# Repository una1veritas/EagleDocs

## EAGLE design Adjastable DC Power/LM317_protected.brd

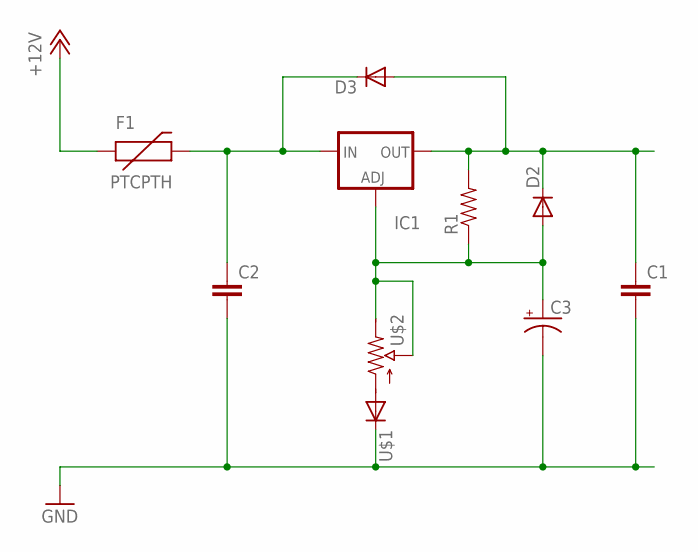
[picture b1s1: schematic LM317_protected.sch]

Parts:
C1, C2: CAPKIT; CAP-PTH-SMALL-KIT
C3: CAP_POLPTH2; CPOL-RADIAL-10UF-25V
D2, D3: DIODEPTH; DIODE-1N4001
F1: PTCPTH; PTC
IC1: LM337TS; 337TS
R1: RESISTORAXIAL-0.3; AXIAL-0.3
U$1: DIODE1N4148; DIODE-1N4148
U$2: POT100K_3362U; 3362U

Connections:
+12V: F1.P$1 (1)
AGND: C1.2, C2.2, C3.2 (-), U$1.C
unnamed: C3.1 (+), D2.A, IC1.1 (ADJ), R1.P$1 (1), U$2.P$1 (E), U$2.P$2 (S)
unnamed: C1.1, D2.C, D3.A, IC1.3 (OUT), R1.P$2 (2)
unnamed: C2.1, D3.C, F1.P$2 (2), IC1.2 (IN)
unnamed: U$1.A, U$2.P$3 (A)

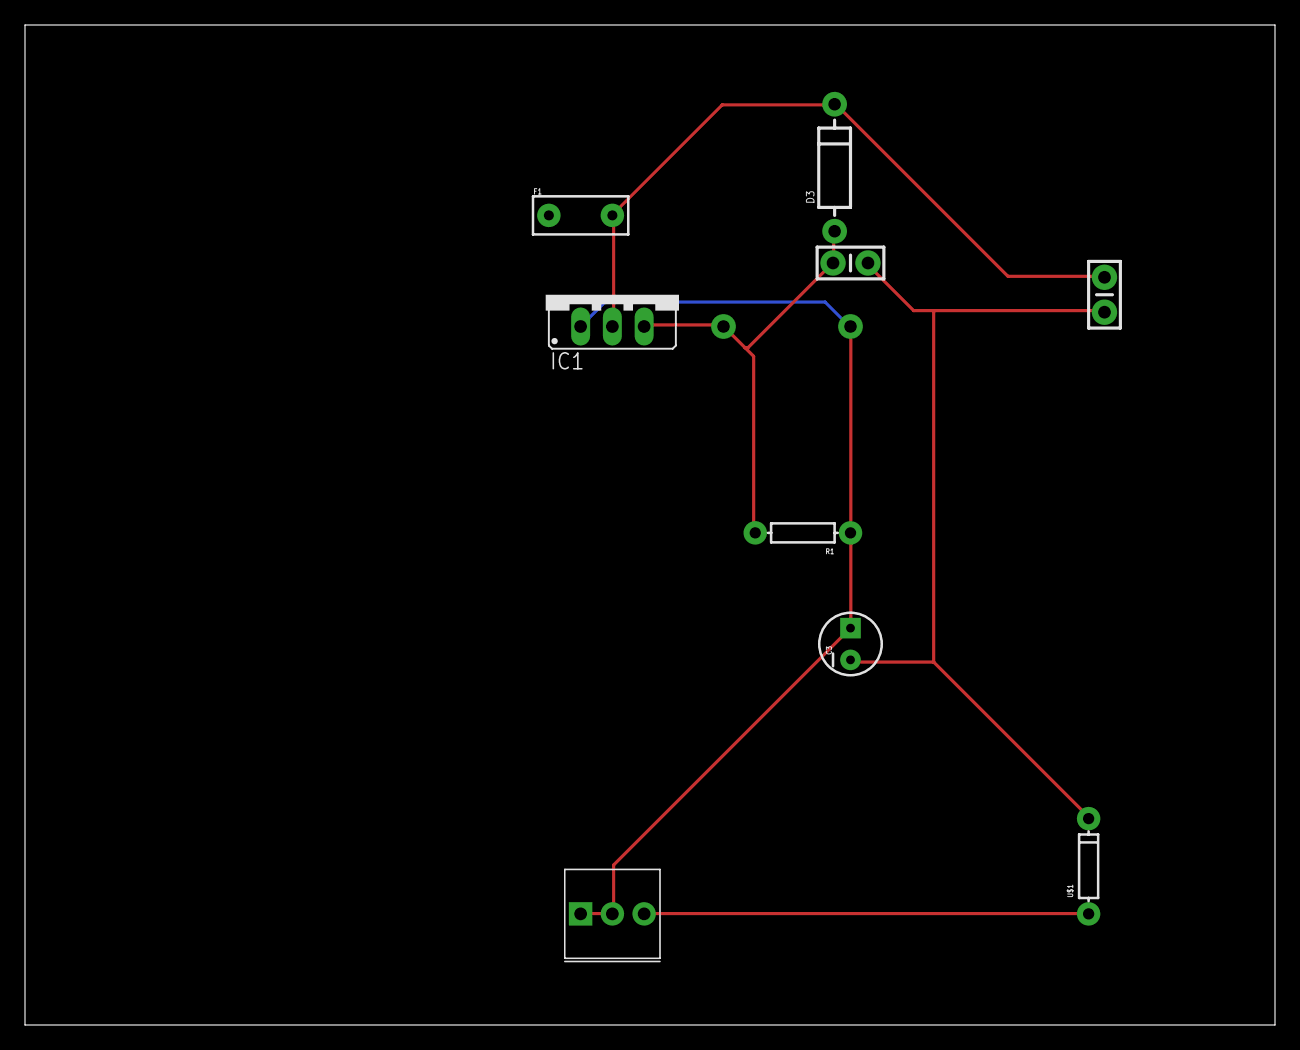
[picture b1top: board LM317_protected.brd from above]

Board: 2 copper layers, 100.0 x 80.0 mm, 10 parts (1 on the bottom side), 5 nets.

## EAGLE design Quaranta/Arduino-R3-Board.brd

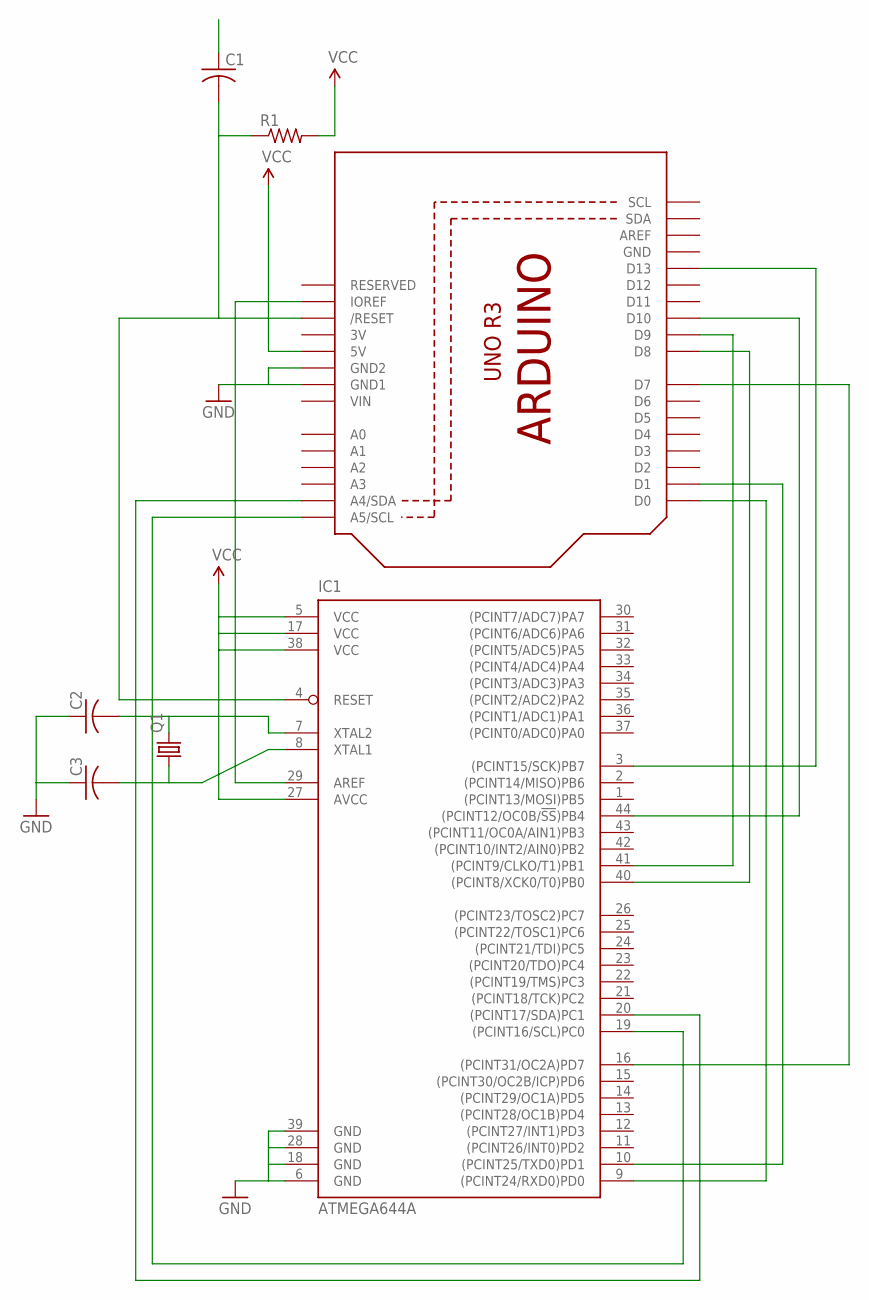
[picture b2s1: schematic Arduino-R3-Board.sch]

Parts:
C1, C2, C3: C-US025-024X044; C025-024X044
IC1: ATMEGA644A; TQFP44
Q1: CRYSTALHC49S; HC49/S
R1: R-US_0204/7; 0204/7
U1: ARDUINOR3-BPLACE

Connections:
3V: U1.3V
GND: C2.1, C3.1, IC1.6 (GND), IC1.18 (GND), IC1.28 (GND), IC1.39 (GND), U1.GND, U1.GND1, U1.GND2
unnamed: C1.2, IC1.4 (RESET), R1.1, U1.RESET (/RESET)
unnamed: IC1.29 (AREF), U1.IOREF
unnamed: IC1.9 ((PCINT24/RXD0)PD0), U1.D0
unnamed: IC1.10 ((PCINT25/TXD0)PD1), U1.D1
unnamed: IC1.16 ((PCINT31/OC2A)PD7), U1.D7
unnamed: IC1.3 ((PCINT15/SCK)PB7), U1.D13
unnamed: IC1.44 ((PCINT12/OC0B/!SS!)PB4), U1.D10
unnamed: IC1.40 ((PCINT8/XCK0/T0)PB0), U1.D8
unnamed: IC1.41 ((PCINT9/CLKO/T1)PB1), U1.D9
unnamed: IC1.19 ((PCINT16/SCL)PC0), U1.A5 (A5/SCL)
unnamed: IC1.20 ((PCINT17/SDA)PC1), U1.A4 (A4/SDA)
unnamed: C2.2, IC1.7 (XTAL2), Q1.2
unnamed: C3.2, IC1.8 (XTAL1), Q1.1
VCC: IC1.5 (VCC), IC1.17 (VCC), IC1.27 (AVCC), IC1.38 (VCC), R1.2, U1.5V
VIN: U1.VIN

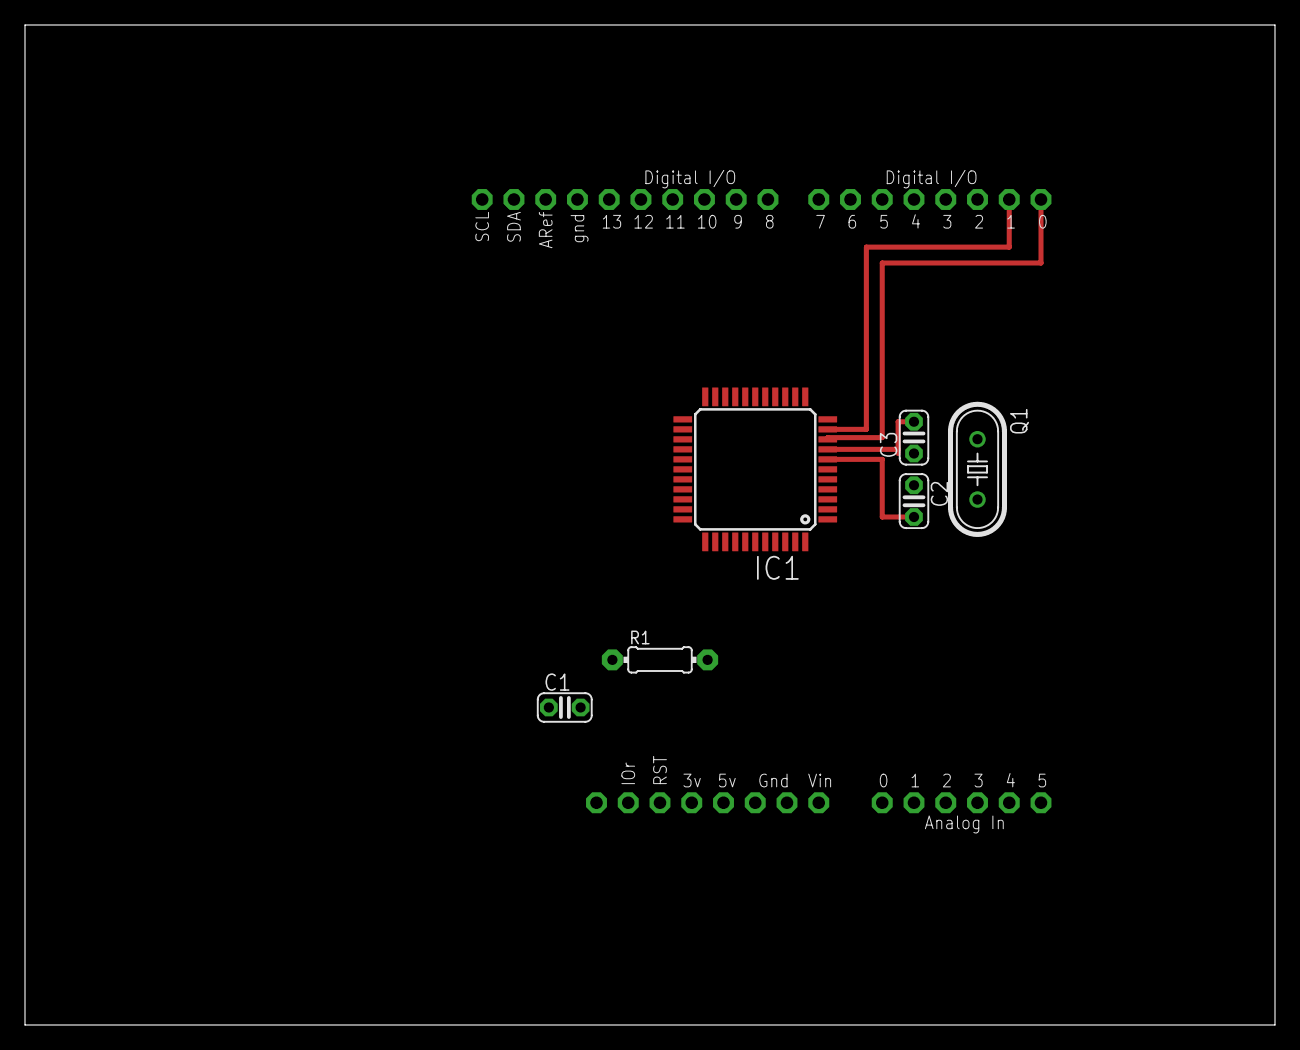
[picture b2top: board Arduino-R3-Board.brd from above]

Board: 2 copper layers, 100.0 x 80.0 mm, 7 parts (0 on the bottom side), 15 nets.

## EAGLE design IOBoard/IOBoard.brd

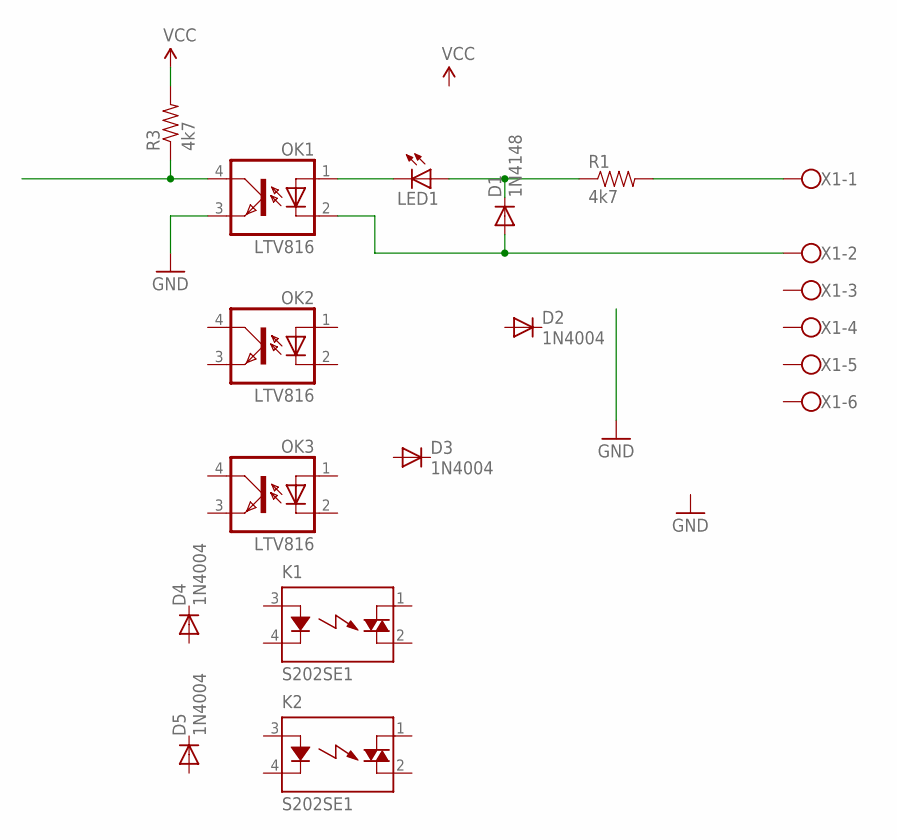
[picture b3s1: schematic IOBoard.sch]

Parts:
D1: 1N4148; DO34-5
D2, D3, D4, D5: 1N4004; DO41-10
K1, K2: S202SE1; S2XXEX
LED1: LED3MM
OK1, OK2, OK3: LTV816; DIL04
R1, R3: 4k7; 1/6W-RES
X1: W237-6

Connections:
GND: OK1.3 (EMIT)
unnamed: LED1.K (C), OK1.1 (A)
unnamed: R1.2, X1.1
unnamed: D1.A, OK1.2 (C), X1.2
unnamed: D1.C, LED1.A, R1.1
unnamed: OK1.4 (COL), R3.1
VCC: R3.2

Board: 2 copper layers, 14 parts (0 on the bottom side), 5 nets, no tracks yet.

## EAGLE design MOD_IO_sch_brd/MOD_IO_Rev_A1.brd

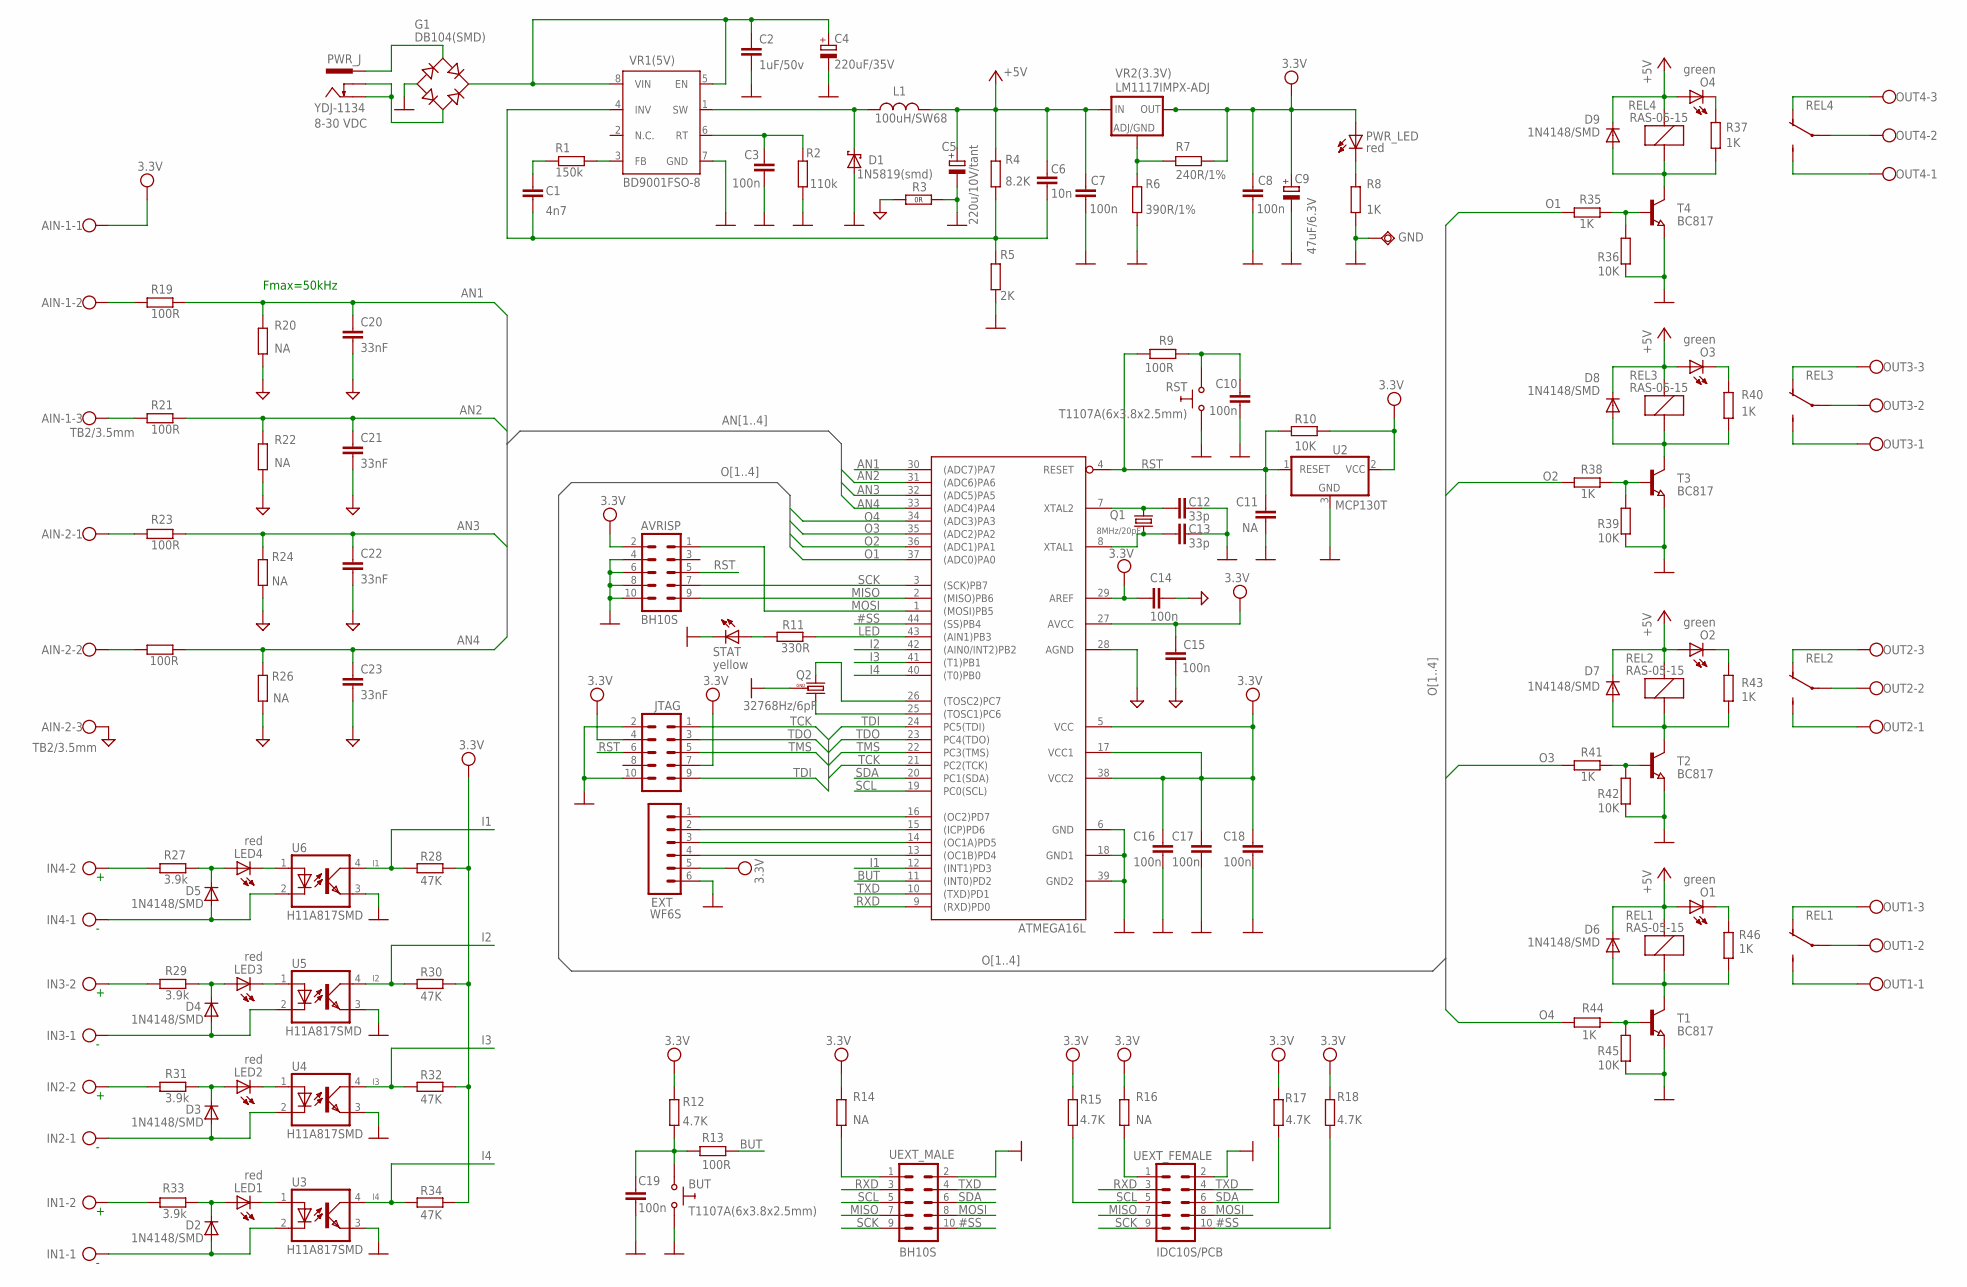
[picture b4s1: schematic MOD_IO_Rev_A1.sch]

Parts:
AIN-1, AIN-2: TB2/3.5mm; CON3-3.5MM
AVRISP: BH10S; CON2X5_SS2
BUT: T1107A(6x3.8x2.5mm); SW-TAKT_6X3.5_SMD
C1: 4n7; C0603
C2: 1uF/50v; C0805
C3, C7, C8, C10, C14, C15, C16, C17, C18, C19: 100n; C0603
C4: 220uF/35V; E3,5-8
C5: 220u/10V/tant; CT7343
C6: 10n; C0603
C9: 47uF/6.3V; CT3528
C11: NA; C0603
C12, C13: 33p; C0603
C20, C21, C22, C23: 33nF; C0603
D1: 1N5819(smd); MLL-41
D2, D3, D4, D5, D6, D7, D8, D9: 1N4148/SMD; SOD80C
EXT: WF6S; CON2.54MM-6-0
G1: DB104(SMD); DB104_SMD
GND: TESTPAD40/70; TESTPAD
IN1, IN2, IN3, IN4: TB2/5MM; W237-102
JTAG: BH10S; CON2X5_SS2
L1: 100uH/SW68; SW68
LED1, LED2, LED3, LED4: red; LED-0805
O1, O2, O3, O4: green; LED-0805
OUT1, OUT2, OUT3, OUT4: TB3/5MM; W237-103
PWR_J: YDJ-1134; PWR_JACK_UNI
PWR_LED: red; LED-0805
Q1: 8MHz/20pF; HC49/SMD2_THIN
Q2: 32768Hz/6pF; TC26H_3_REPAIR
R1: 150k; R0603
R2: 110k; R0603
R3: R_0R0R(NA); 0603_0R
R4: 8.2K; R0603
R5: 2K; R0603
R6: 390R/1%; R0603
R7: 240R/1%; R0603
R8, R35, R37, R38, R40, R41, R43, R44, R46: 1K; R0603
R9, R13, R19, R21, R23, R25: 100R; R0603
R10, R36, R39, R42, R45: 10K; R0603
R11: 330R; R0603
R12, R15, R17, R18: 4.7K; R0603
R14, R16, R20, R22, R24, R26: NA; R0603_NA
R27, R29, R31, R33: 3.9k; R0603
R28, R30, R32, R34: 47K; R0603
REL1, REL2, REL3, REL4: RAS-05-15; H200-FAT
RST: T1107A(6x3.8x2.5mm); SW-TAKT_6X3.5_SMD
STAT: yellow; LED-0805
T1, T2, T3, T4: BC817; SOT23
U1: ATMEGA16L; 44TQFP
U2: MCP130T; SOT23
U3, U4, U5, U6: H11A817SMD; OPTOCOUPLER_SMD4PIN
UEXT_FEMALE: IDC10S/PCB; ML10L_PADS_FEMAIL
UEXT_MALE: BH10S; ML10_PADS
VR1(5V): BD9001FSO-8; SO-8
VR2(3.3V): LM1117IMPX-ADJ; SOT223

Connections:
#SS: R18.1, U1.44 ((SS)PB4), UEXT_FEMALE.10, UEXT_MALE.10
+5V: C5.+, C6.1, C7.2, D6.C, D7.C, D8.C, D9.C, L1.2, O1.A, O2.A, O3.A, O4.A, R4.1, REL1.1, REL2.1, REL3.1, REL4.1, VR2(3.3V).3 (IN)
AGND: AIN-2.3, C14.2, C15.1, C20.2, C21.2, C22.2, C23.2, R3.1 (1.1), R20.1, R22.1, R24.1, R26.1, U1.28 (AGND)
AN1: C20.1, R19.2, R20.2, U1.30 ((ADC7)PA7)
AN2: C21.1, R21.2, R22.2, U1.31 ((ADC6)PA6)
AN3: C22.1, R23.2, R24.2, U1.32 ((ADC5)PA5)
AN4: C23.1, R25.1, R26.2, U1.33 ((ADC4)PA4)
BUT: R13.2, U1.11 ((INT0)PD2)
GND: AVRISP.4, AVRISP.6, AVRISP.8, AVRISP.10, BUT.P$1 (0), C2.2, C3.1, C4.-, C5.-, C7.1, C8.1, C9.-, C10.2, C11.2, C12.1, C13.1, C16.2, C17.2, C18.2, C19.2, D1.A, EXT.6, G1.-, GND.P$1, JTAG.2, JTAG.10, Q2.GND, R2.2, R3.2 (1.2), R5.2, R6.2, R8.2, R36.1, R39.1, R42.1, R45.1, RST.P$1 (0), STAT.C, T1.2 (E), T2.2 (E), T3.2 (E), T4.2 (E), U1.6 (GND), U1.18 (GND1), U1.39 (GND2), U2.3 (GND), U3.3 (EMI), U4.3 (EMI), U5.3 (EMI), U6.3 (EMI), UEXT_FEMALE.2, UEXT_MALE.2, VR1(5V).7 (GND)
I1: R28.1, U1.12 ((INT1)PD3), U6.4 (COL)
I2: R30.1, U1.42 ((AIN0/INT2)PB2), U5.4 (COL)
I3: R32.1, U1.41 ((T1)PB1), U4.4 (COL)
I4: R34.1, U1.40 ((T0)PB0), U3.4 (COL)
LED: R11.1, U1.43 ((AIN1)PB3)
MISO: AVRISP.9, U1.2 ((MISO)PB6), UEXT_FEMALE.7, UEXT_MALE.7
MOSI: AVRISP.1, U1.1 ((MOSI)PB5), UEXT_FEMALE.8, UEXT_MALE.8
unnamed: BUT.P$2 (1), C19.1, R12.2, R13.1
unnamed: R16.1, UEXT_FEMALE.1
unnamed: OUT2.2, REL2.P
unnamed: OUT2.1, REL2.S
unnamed: OUT4.3, REL4.O
unnamed: OUT1.2, REL1.P
unnamed: OUT1.1, REL1.S
unnamed: IN4.2, R27.1
unnamed: IN3.2, R29.1
unnamed: IN2.2, R31.1
unnamed: IN1.2, R33.1
unnamed: R14.1, UEXT_MALE.1
unnamed: EXT.1, U1.16 ((OC2)PD7)
unnamed: C10.1, R9.1, RST.P$2 (1)
unnamed: OUT4.2, REL4.P
unnamed: OUT4.1, REL4.S
unnamed: R35.2, R36.2, T4.1 (B)
unnamed: OUT3.3, REL3.O
unnamed: D9.A, R37.1, REL4.2, T4.3 (C)
unnamed: OUT3.2, REL3.P
unnamed: OUT3.1, REL3.S
unnamed: R38.2, R39.2, T3.1 (B)
unnamed: O4.C, R37.2
unnamed: O3.C, R40.2
unnamed: C12.2, Q1.2, U1.7 (XTAL2)
unnamed: OUT2.3, REL2.O
unnamed: EXT.2, U1.15 ((ICP)PD6)
unnamed: EXT.3, U1.14 ((OC1A)PD5)
unnamed: R41.2, R42.2, T2.1 (B)
unnamed: O1.C, R46.2
unnamed: D8.A, R40.1, REL3.2, T3.3 (C)
unnamed: EXT.4, U1.13 ((OC1B)PD4)
unnamed: OUT1.3, REL1.O
unnamed: R44.2, R45.2, T1.1 (B)
unnamed: C1.1, C6.2, R4.2, R5.1, VR1(5V).4 (INV)
unnamed: O2.C, R43.2
unnamed: D7.A, R43.1, REL2.2, T2.3 (C)
unnamed: D6.A, R46.1, REL1.2, T1.3 (C)
unnamed: R1.1, VR1(5V).3 (FB)
unnamed: R11.2, STAT.A
unnamed: G1.AC1, PWR_J.-, PWR_J.--
unnamed: G1.AC2, PWR_J.+
unnamed: AIN-1.2, R19.1
unnamed: C13.2, Q1.1, U1.8 (XTAL1)
unnamed: AIN-2.2, R25.2
unnamed: C1.2, R1.2
unnamed: R6.1, R7.1, VR2(3.3V).1 (ADJ/GND)
unnamed: AIN-1.3, R21.1
unnamed: PWR_LED.C, R8.1
unnamed: AIN-2.1, R23.1
unnamed: C2.1, C4.+, G1.+, VR1(5V).5 (EN), VR1(5V).8 (VIN)
unnamed: C3.2, R2.1, VR1(5V).6 (RT)
unnamed: D4.A, IN3.1, U5.2 (C)
unnamed: LED3.C, U5.1 (A)
unnamed: D5.C, LED4.A, R27.2
unnamed: D5.A, IN4.1, U6.2 (C)
unnamed: D1.K (C), L1.1, VR1(5V).1 (SW)
unnamed: LED4.C, U6.1 (A)
unnamed: D4.C, LED3.A, R29.2
unnamed: D2.A, IN1.1, U3.2 (C)
unnamed: Q2.1, U1.26 ((TOSC2)PC7)
unnamed: LED1.C, U3.1 (A)
unnamed: D3.C, LED2.A, R31.2
unnamed: D3.A, IN2.1, U4.2 (C)
unnamed: Q2.2, U1.25 ((TOSC1)PC6)
unnamed: LED2.C, U4.1 (A)
unnamed: D2.C, LED1.A, R33.2
O1: R35.1, U1.37 ((ADC0)PA0)
O2: R38.1, U1.36 ((ADC1)PA1)
O3: R41.1, U1.35 ((ADC2)PA2)
O4: R44.1, U1.34 ((ADC3)PA3)
RST: AVRISP.5, C11.1, JTAG.6, R9.2, R10.2, U1.4 (RESET), U2.1 (RESET)
RXD: U1.9 ((RXD)PD0), UEXT_FEMALE.3, UEXT_MALE.3
SCK: AVRISP.7, U1.3 ((SCK)PB7), UEXT_FEMALE.9, UEXT_MALE.9
SCL: R15.1, U1.19 (PC0(SCL)), UEXT_FEMALE.5, UEXT_MALE.5
SDA: R17.1, U1.20 (PC1(SDA)), UEXT_FEMALE.6, UEXT_MALE.6
TCK: JTAG.1, U1.21 (PC2(TCK))
TDI: JTAG.9, U1.24 (PC5(TDI))
TDO: JTAG.3, U1.23 (PC4(TDO))
TMS: JTAG.5, U1.22 (PC3(TMS))
TXD: U1.10 ((TXD)PD1), UEXT_FEMALE.4, UEXT_MALE.4
VCC: AIN-1.1, AVRISP.2, C8.2, C9.+, C14.1, C15.2, C16.1, C17.1, C18.1, EXT.5, JTAG.4, JTAG.7, PWR_LED.A, R7.2, R10.1, R12.1, R14.2, R15.2, R16.2, R17.2, R18.2, R28.2, R30.2, R32.2, R34.2, U1.5 (VCC), U1.17 (VCC1), U1.27 (AVCC), U1.29 (AREF), U1.38 (VCC2), U2.2 (VCC), VR2(3.3V).2 (OUT), VR2(3.3V).4 (RAD)

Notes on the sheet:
8-30 VDC
Fmax=50kHz

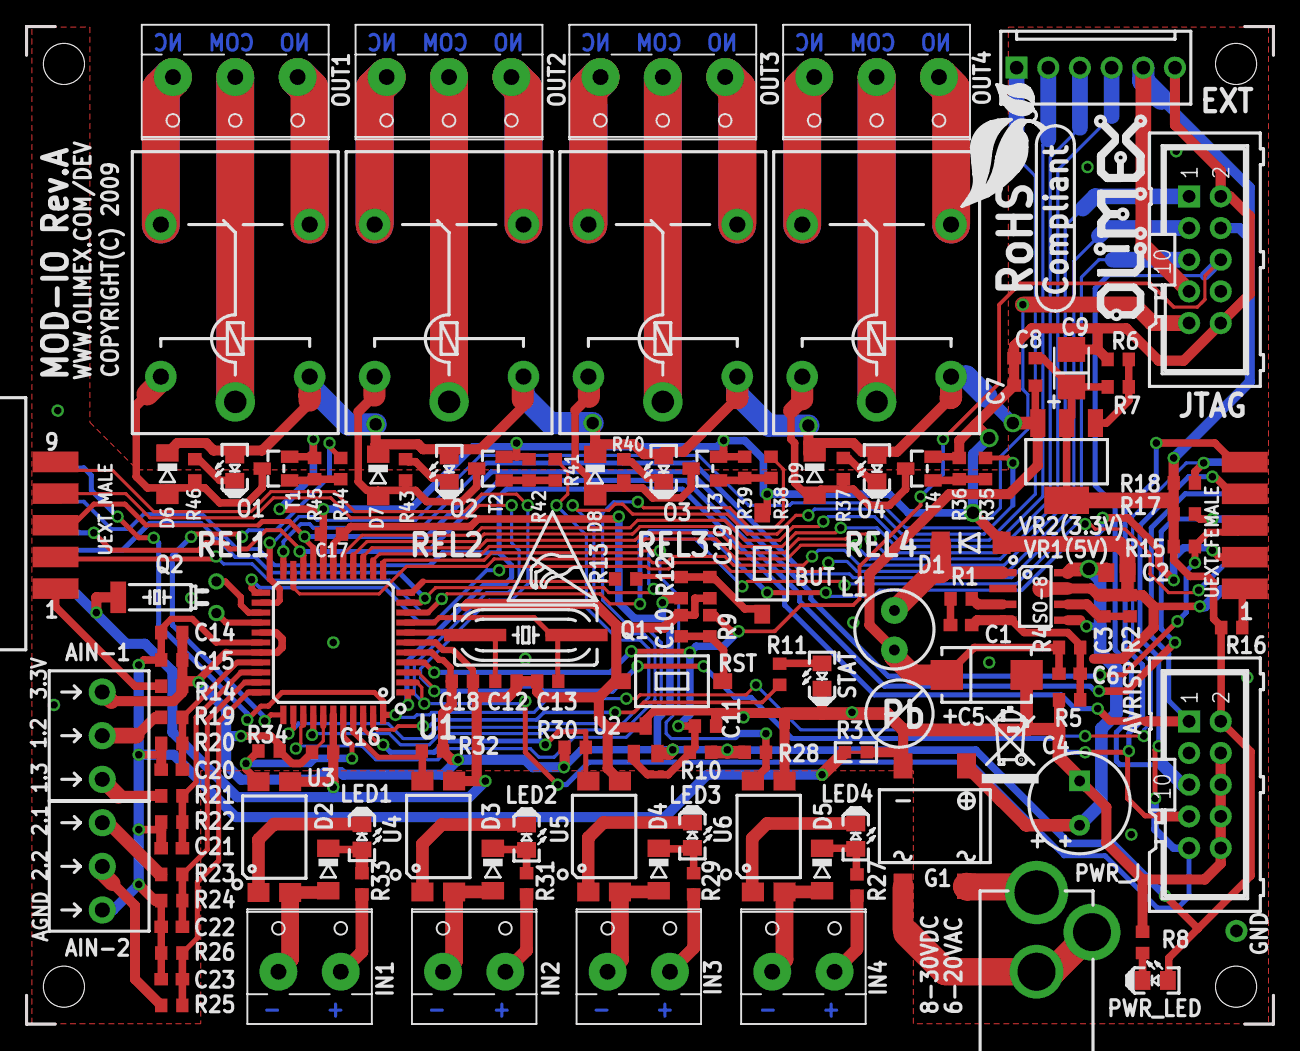
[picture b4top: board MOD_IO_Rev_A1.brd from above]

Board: 2 copper layers, 100.0 x 80.0 mm, 132 parts (1 on the bottom side), 98 nets.

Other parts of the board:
U$1: RECYCLE_BIN1/8
U$3: ESD_SYMBOL
U$4: PB
U$5: ROHS
U$6: OLIMEX1_V

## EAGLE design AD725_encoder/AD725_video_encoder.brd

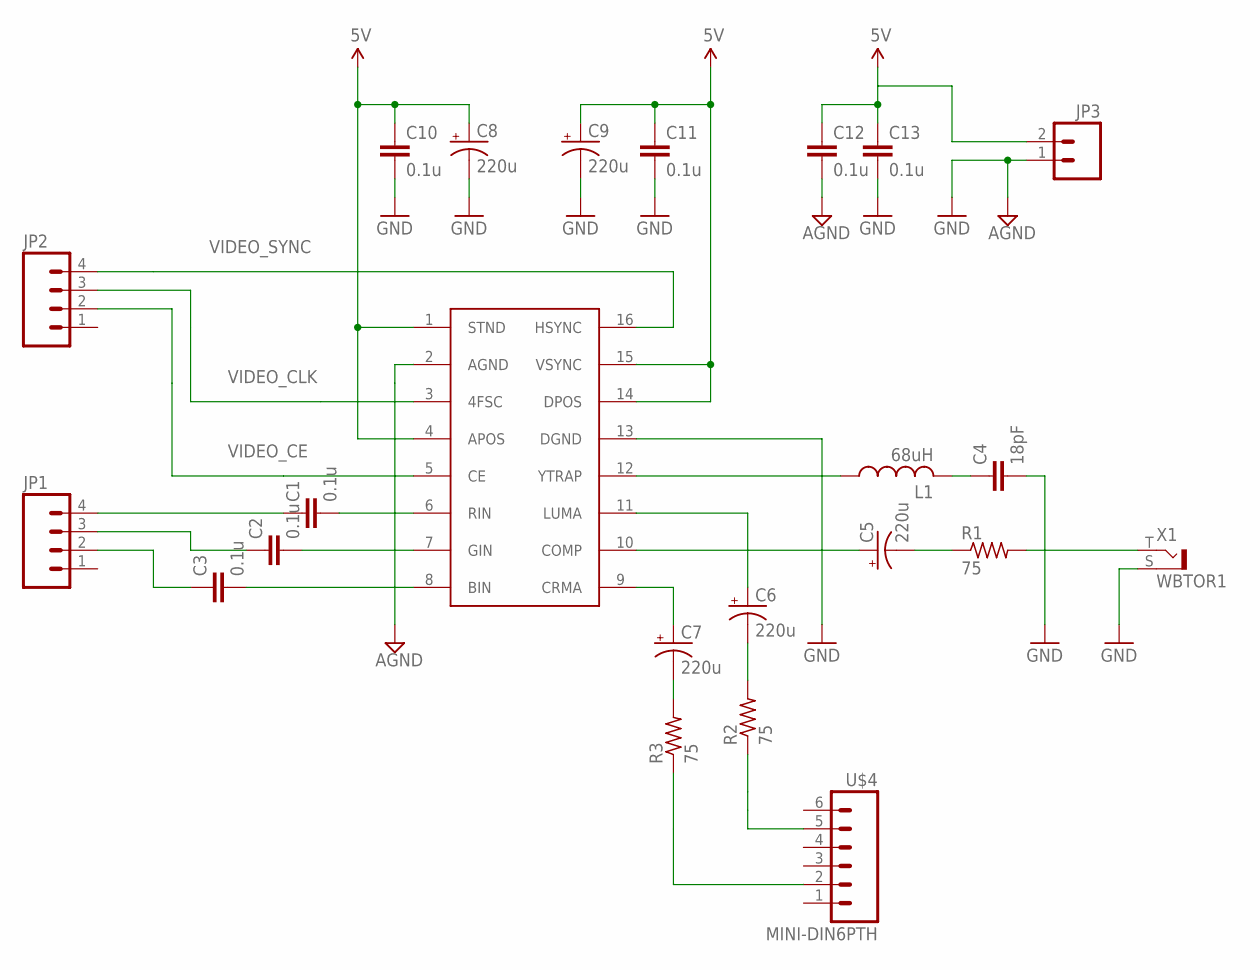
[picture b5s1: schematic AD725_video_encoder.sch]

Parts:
C1, C2, C3, C10, C11, C12, C13: 0.1u; CAP-PTH-SMALL-KIT
C4: 18pF; CAP-PTH-SMALL-KIT
C5, C6, C7, C8, C9: 220u; E2-4
JP1, JP2: M04PTH; 1X04
JP3: M02POLAR; MOLEX-1X2
L1: 68uH; 0207/2V
R1, R2, R3: 75; 0204/5
U$1: AD725; SO16W
U$4: MINI-DIN6PTH; MINI-DIN6
X1: WBTOR1

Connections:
5V: C8.+, C9.+, C10.1, C11.1, C12.1, C13.1, JP3.2, U$1.1 (STND), U$1.4 (APOS), U$1.14 (DPOS), U$1.15 (VSYNC)
AGND: C12.2, U$1.2 (AGND)
GND: C4.2, C8.-, C9.-, C10.2, C11.2, C13.2, JP3.1, U$1.13 (DGND), X1.S
unnamed: C1.2, U$1.6 (RIN)
unnamed: C2.2, U$1.7 (GIN)
unnamed: C3.2, U$1.8 (BIN)
unnamed: C3.1, JP1.2
unnamed: C2.1, JP1.3
unnamed: C1.1, JP1.4
unnamed: C7.-, R3.2
unnamed: C6.-, R2.2
unnamed: L1.1, U$1.12 (YTRAP)
unnamed: C4.1, L1.2
unnamed: C5.+, U$1.10 (COMP)
unnamed: C5.-, R1.1
unnamed: C7.+, U$1.9 (CRMA)
unnamed: R1.2, X1.T
unnamed: C6.+, U$1.11 (LUMA)
unnamed: R3.1, U$4.2
unnamed: R2.1, U$4.5
VIDEO_CE: JP2.2, U$1.5 (CE)
VIDEO_CLK: JP2.3, U$1.3 (4FSC)
VIDEO_SYNC: JP2.4, U$1.16 (HSYNC)

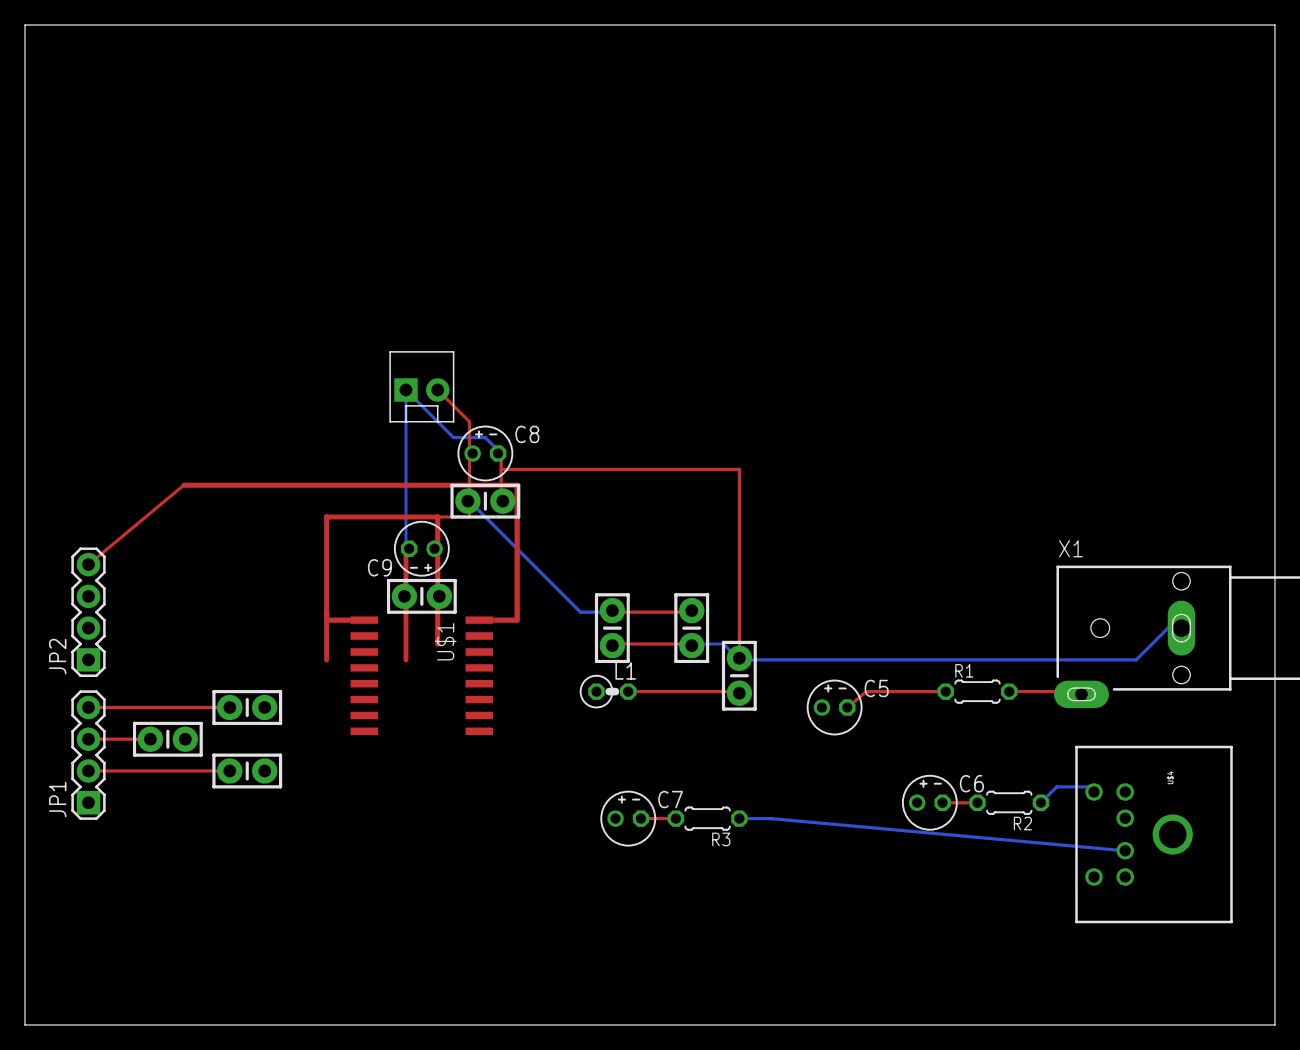
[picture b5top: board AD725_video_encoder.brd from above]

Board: 2 copper layers, 100.0 x 80.0 mm, 23 parts (0 on the bottom side), 23 nets.

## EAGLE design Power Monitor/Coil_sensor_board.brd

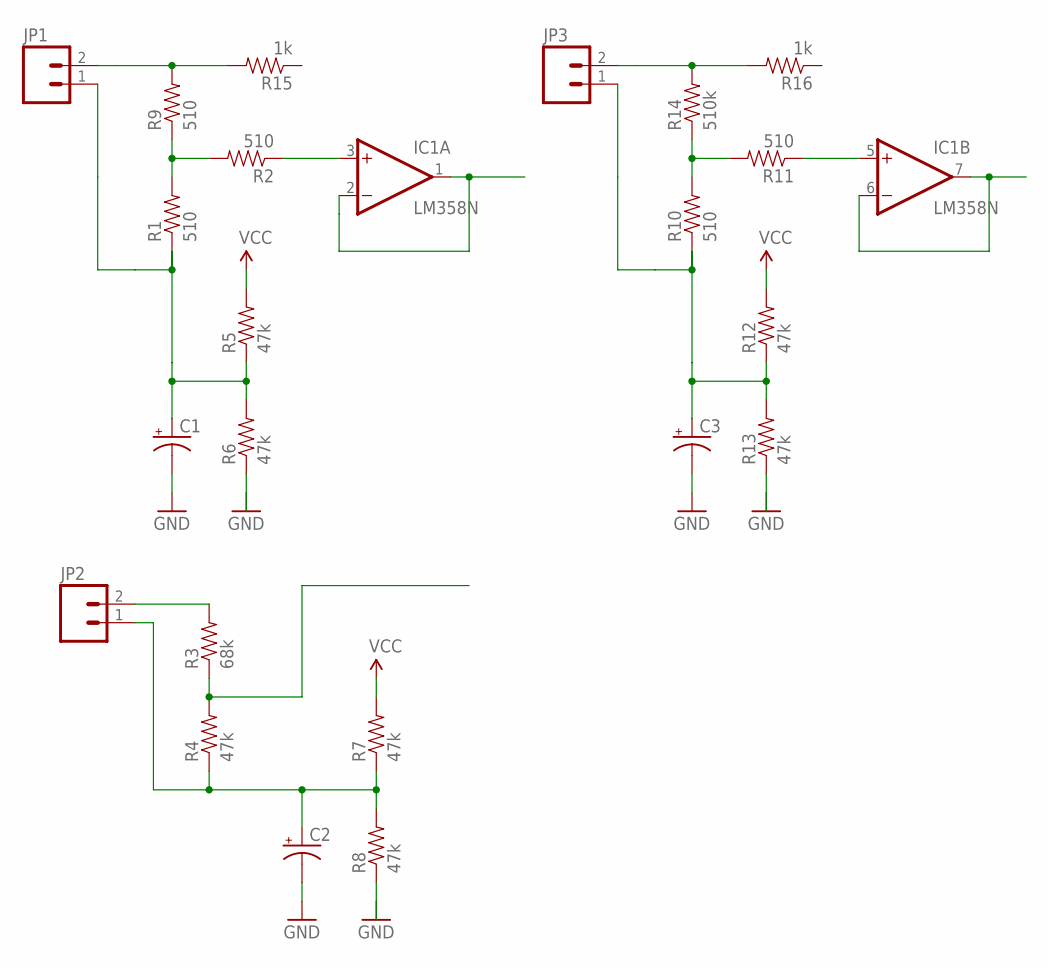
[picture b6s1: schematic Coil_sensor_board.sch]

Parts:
C1, C2, C3: CAP_POLPTH1; CPOL-RADIAL-100UF-25V
IC1: LM358N; DIL08
JP1, JP2, JP3: M02PTH; 1X02
R1, R2, R9, R10, R11: 510; 1/6W-RES
R3: 68k; 1/6W-RES
R4, R5, R6, R7, R8, R12, R13: 47k; 1/6W-RES
R14: 510k; 1/6W-RES
R15, R16: 1k; 1/6W-RES

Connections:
GND: C1.2 (-), C2.2 (-), C3.2 (-), R6.1, R8.1, R13.1
unnamed: C1.1 (+), JP1.1, R1.1, R5.1, R6.2
unnamed: IC1.3 (+IN), R2.1
unnamed: JP1.2, R9.2, R15.2
unnamed: C3.1 (+), JP3.1, R10.1, R12.1, R13.2
unnamed: JP2.2, R3.2
unnamed: IC1.1 (OUT), IC1.2 (-IN)
unnamed: R1.2, R2.2, R9.1
unnamed: IC1.5 (+IN), R11.1
unnamed: C2.1 (+), JP2.1, R4.1, R7.1, R8.2
unnamed: R10.2, R11.2, R14.1
unnamed: R3.1, R4.2
unnamed: JP3.2, R14.2, R16.2
unnamed: IC1.6 (-IN), IC1.7 (OUT)
V+: IC1.8 (V+)
V-: IC1.4 (V-)
VCC: R5.2, R7.2, R12.2

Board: 2 copper layers, 23 parts (0 on the bottom side), 15 nets, no tracks yet.

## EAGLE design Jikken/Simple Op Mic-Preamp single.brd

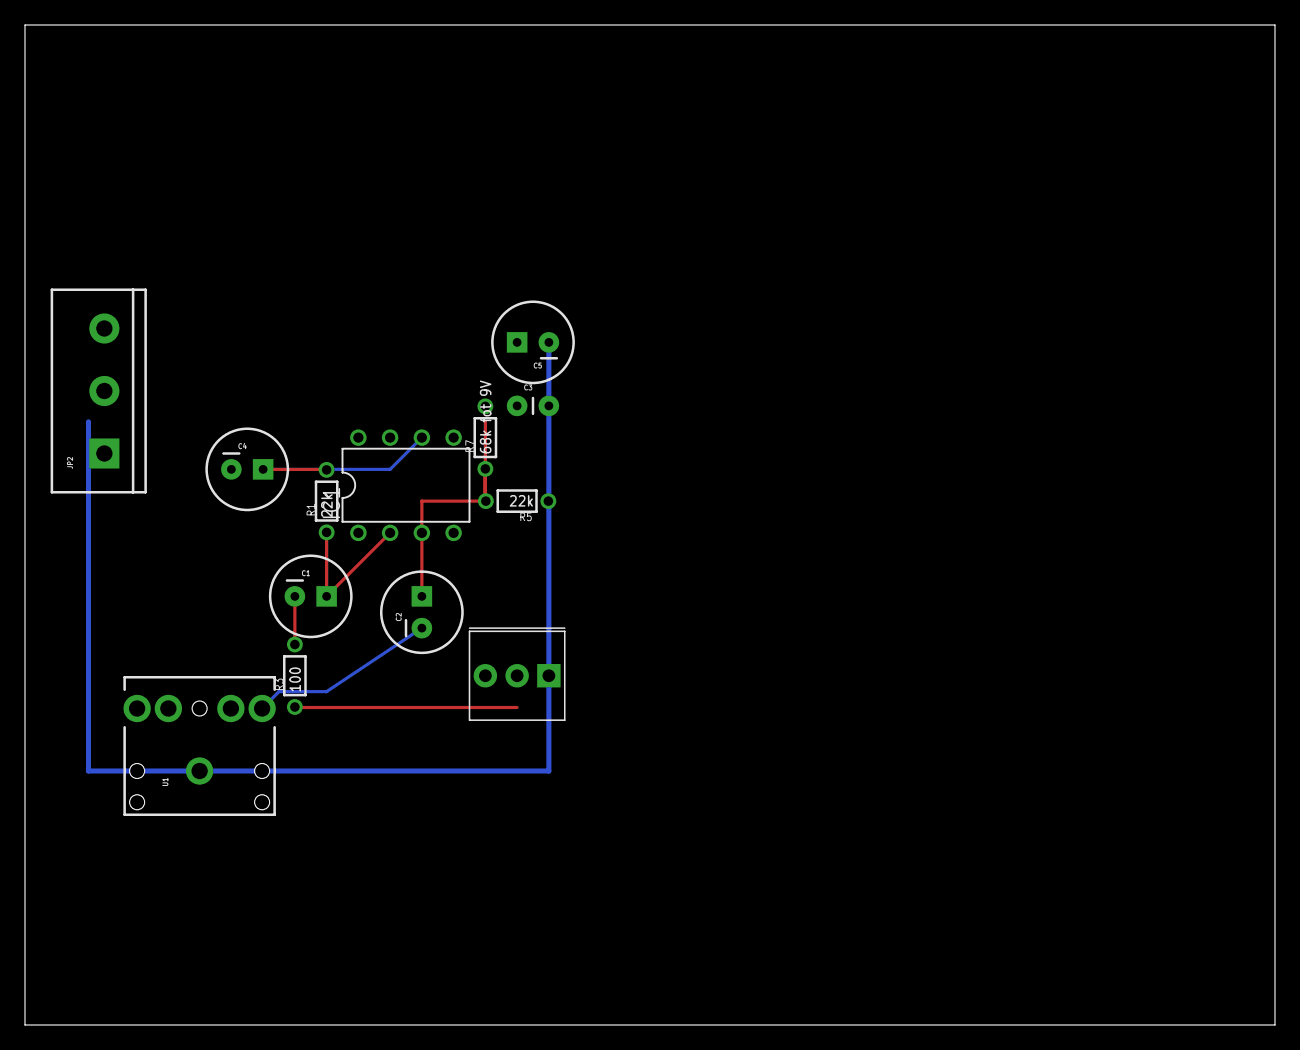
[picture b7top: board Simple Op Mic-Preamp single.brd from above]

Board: 2 copper layers, 100.0 x 80.0 mm, 13 parts (0 on the bottom side), 9 nets.

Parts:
C1, C2, C4: 10u; CPOL-RADIAL-100UF-25V
C3: 0.1uF; CAP-PTH-SMALL
C5: 100u; CPOL-RADIAL-100UF-25V
IC1: LF356N; DIL08
JP2: SCREWTERMINAL-5MM-3
R1, R5: 22k; 1/6W-RES
R3: 100; 1/6W-RES
R7: 68k fot 9V; 1/6W-RES
TRIMPOT: 20k; 3362U
U1: AUDIO-JACK

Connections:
GND: C3.2, C5.2, IC1.4, JP2.1, R5.1, TRIMPOT.P$1, U1.SLEEVE
unnamed: C1.2, R3.2
unnamed: C4.1, IC1.6, R1.2
unnamed: R3.1, TRIMPOT.P$2, TRIMPOT.P$3
unnamed: C1.1, IC1.2, R1.1
unnamed: C2.1, IC1.3, R5.2, R7.1
unnamed: C2.2, U1.TIP
unnamed: C4.2, JP2.2
VCC: C3.1, C5.1, IC1.7, JP2.3, R7.2

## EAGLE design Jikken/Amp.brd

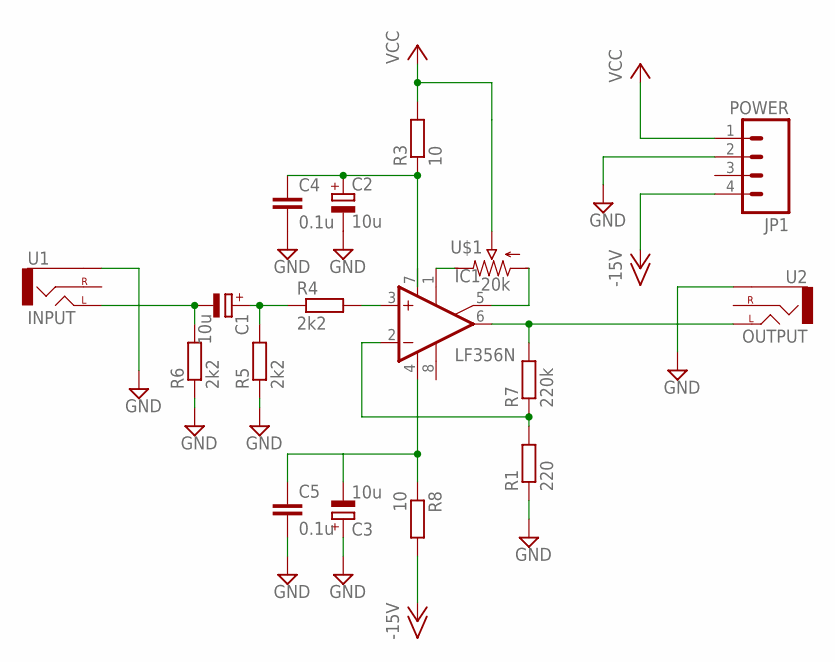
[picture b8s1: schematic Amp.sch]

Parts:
C1, C2, C3: 10u; E1,8-4
C4, C5: 0.1u; C025-024X044
IC1: LF356N; DIL08
JP1: POWER; MOLEX-1X4
R1: 220; 0204/5
R3, R8: 10; 0204/5
R4, R5, R6: 2k2; 0204/5
R7: 220k; 0204/5
U1: INPUT; STEREOJACK2.5MM_SPECIAL_HOLES-ONLY
U2: OUTPUT; STEREOJACK2.5MM_SPECIAL_HOLES-ONLY
U$1: 20k; 3362U

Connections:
-15V: JP1.4, R8.2
GND: C2.-, C3.+, C4.2, C5.2, JP1.2, R1.1, R5.1, R6.1, U1.RING1 (SLEEVE), U2.RING1 (SLEEVE)
unnamed: C1.-, R6.2, U1.SHIELD (LEFT)
unnamed: C1.+, R4.1, R5.2
unnamed: IC1.2 (-IN), R1.2, R7.1
unnamed: C3.-, C5.1, IC1.4 (V-), R8.1
unnamed: IC1.3 (+IN), R4.2
unnamed: IC1.6 (OUT), R7.2, U2.SHIELD (LEFT)
unnamed: C2.+, C4.1, IC1.7 (V+), R3.1
unnamed: IC1.5 (ON2), U$1.P$3 (A)
unnamed: IC1.1 (ON1), U$1.P$1 (E)
VCC: JP1.1, R3.2, U$1.P$2 (S)

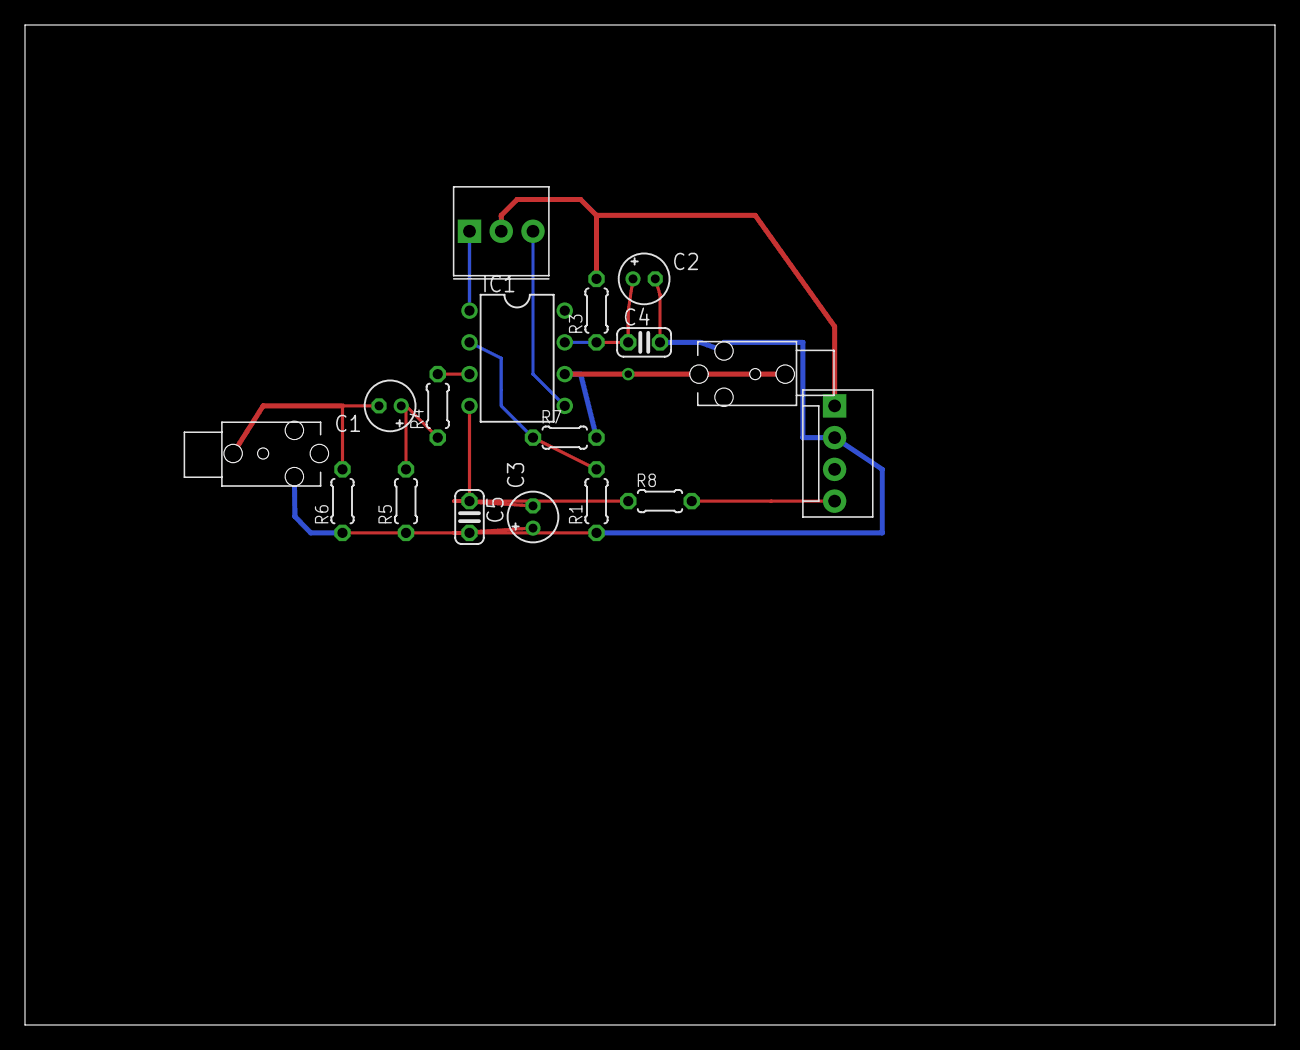
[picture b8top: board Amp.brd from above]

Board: 2 copper layers, 100.0 x 80.0 mm, 17 parts (0 on the bottom side), 12 nets.

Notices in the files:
MOD_IO_sch_brd/MOD_IO_Rev_A1.brd:
COPYRIGHT(C) 2009
MOD_IO_sch_brd/MOD_IO_Rev_A1.sch:
This hardware design by Olimex LTD is licensed under a Creative Commons Attribution-ShareAlike 3.0 Unported License.
parts and their libraries:
SparkFun: Licensing: CC v3.0 Share-Alike You are welcome to use this library for commercial purposes.
